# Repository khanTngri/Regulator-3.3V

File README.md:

# Breadboard Power Supply — 3.3V Regulator (USB-C Powered)

A simple open-hardware power supply module designed to provide a clean and stable **3.3 V** output for breadboard prototyping.  
Powered directly from a **USB-C 5 V** input.

The project is made in **KiCad 9** and includes an **interactive HTML BOM** for quick assembly and part identification.

---

## Features
- USB-C 5 V input (VBUS)
- 3.3 V LDO regulator output
- Compact PCB size, optimized for breadboard use
- Easy-to-source components
- Interactive BOM (`ibom.html`) included
- Open-hardware design (licensed under CERN OHL v1.2)

---

## Electrical Specifications

| Parameter | Value |
|----------|--------|
| Input voltage | 5 V (USB-C VBUS) |
| Output voltage | 3.3 V |
| Regulator type | LDO (linear) |
| Typical output current | depends on LDO (typically 300–800 mA) |

---

## Interactive BOM
Open the file `ibom.html` in your web browser to view:
- all components with footprints,
- live board highlight,
- part positions,
- grouped components.

---

## License
This hardware design is licensed under the **CERN OHL v.1.2**.  
See the `LICENSE` file for details.

If you manufacture products based on this design,  
please notify me according to section 4.2 of the license.

---

##  Contact
For questions, suggestions, or manufacturing notification:  
**<theshine777@gmail.com>**

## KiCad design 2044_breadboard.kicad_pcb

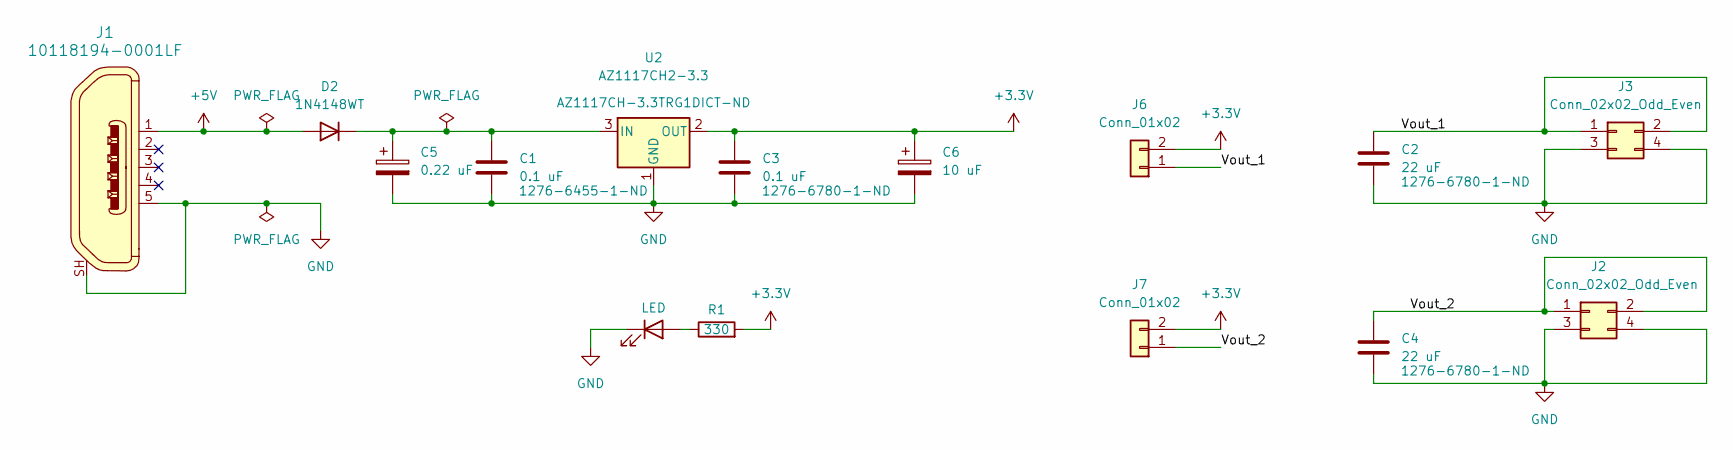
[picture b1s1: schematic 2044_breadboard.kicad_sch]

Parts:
C1: 0.1 uF; C_0805_2012Metric_Pad1.18x1.45mm_HandSolder; DigiKey 1276-6455-1-ND
C2, C4: 22 uF; C_0805_2012Metric_Pad1.18x1.45mm_HandSolder; DigiKey 1276-6780-1-ND
C3: 0.1 uF; C_0805_2012Metric_Pad1.18x1.45mm_HandSolder; DigiKey 1276-6780-1-ND
C5: 0.22 uF; CP_Radial_D4.0mm_P1.50mm
C6: 10 uF; CP_Radial_D5.0mm_P2.00mm
D1: LED; LED_D3.0mm
D2: 1N4148WT; D_SOD-523
J1: 10118194-0001LF; USB_Micro_B_Female_10118194-0001LF; MPN 10118194-0001LF; Digi-Key_PN 609-4618-1-ND
J2, J3: Conn_02x02_Odd_Even; PinHeader_2x02_P2.54mm_Vertical
J6, J7: Conn_01x02; PinHeader_1x02_P1.00mm_Vertical
R1: 330; R_0805_2012Metric_Pad1.20x1.40mm_HandSolder
U2: AZ1117CH2-3.3; SOT-223-3_TabPin2; DigiKey AZ1117CH-3.3TRG1DICT-ND

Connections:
+3.3V: C3.1, C6.1, J6.2, J7.2, R1.2, U2.2 (OUT)
+5V: D2.2 (A), J1.1
/Vout_1: C2.1, J3.1, J3.2, J6.1
/Vout_2: C4.1, J2.1, J2.2, J7.1
GND: C1.2, C2.2, C3.2, C4.2, C5.2, C6.2, D1.1 (K), J1.5, J1.SH, J2.3, J2.4, J3.3, J3.4, U2.1 (GND)
unnamed: D1.2 (A), R1.1
unnamed: C1.1, C5.1, D2.1 (K), U2.3 (IN)

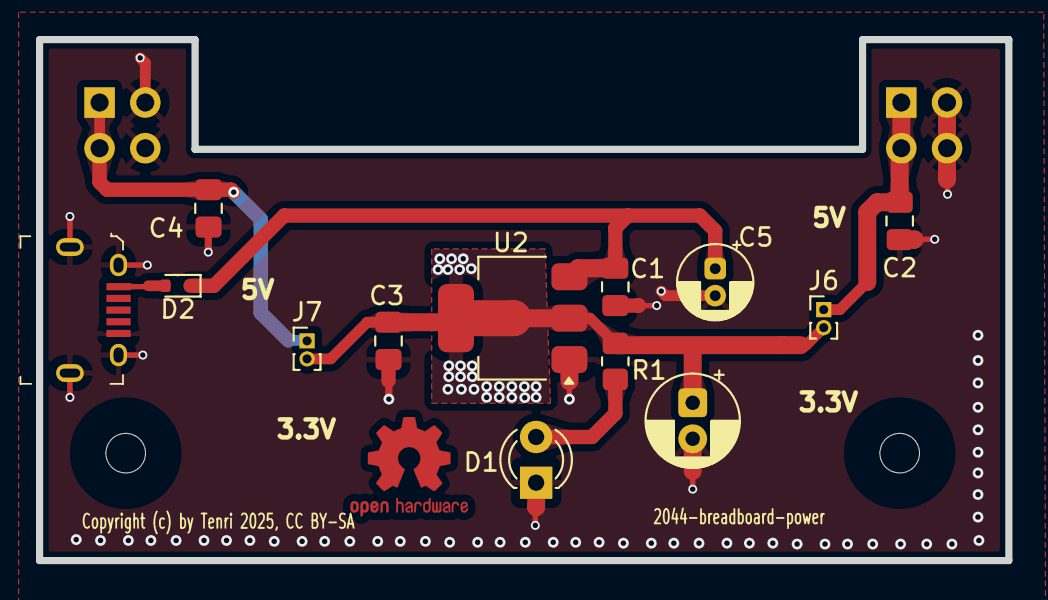
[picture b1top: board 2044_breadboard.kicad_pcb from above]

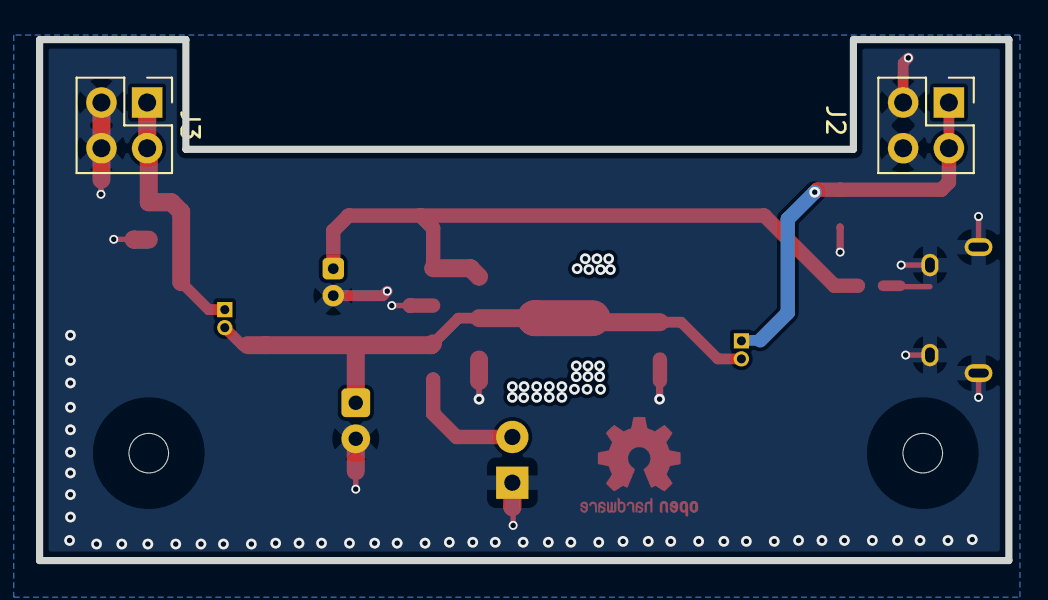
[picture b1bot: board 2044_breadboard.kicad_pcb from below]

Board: 2 copper layers, 53.8 x 28.9 mm, 15 parts (2 on the bottom side), 7 nets.

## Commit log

2025-11-15 Initial commit: KiCad 3.3V regulator project
2025-11-15 Create License

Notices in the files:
2044_breadboard.kicad_pcb:
Copyright (c) by Tenri 2025, CC BY-SA
